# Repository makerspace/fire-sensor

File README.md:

# Fire sensor for Stockholm Makerspace

This ESP32-based sensor monitors the fire-safety system of the [big dust collector](https://wiki.makerspace.se/Sp%C3%A5nsug,_Felder_RL_125) in the [Stockholm Makerspace](https://makerspace.se) Wood Workshop.
If a fire is detected, a POST request is sent to a URL, which will (presumably) then notify people that something bad is happening.

It monitors:

* A temperature sensor.
* A relay for the pressure sensor on the fire-safety system's water tank.
* A distance sensor, used for measuring the amount of dust in the dust bin.
* A relay for the distance sensor.

## Installation

### Pre-requisites

```bash
# Use Linux. It might be compatible with macOS, but likely not.

# Install rust
open https://rustup.rs/

cargo install ldproxy

# Install espup to manage the esp toolchain
cargo install espup --locked

# Install the esp toolchain
espup install

# Install espflash wrapper for cargo
cargo install cargo-espflash

# Clone this repository
git clone https://github.com/makerspace/fire-sensor.git
cd fire-sensor
```

### Flashing the ESP

The ESP supports both flashing via USB, and updates over wifi.

To flash via a connected USB cable, use
```bash
make flash
```

To flash to a powered-on ESP32 module on the same network, use:
```bash
make ota
```

Note: The MAC-address of the ESP32 module is hardcoded in the Makefile.

Note: The ESP32 will connect to the *Stockholm Makerspace Wifi* on startup. You must be on this network to be able to flash it wirelessly.

If the flash failed and the ESP32 cannot start properly, it will automatically revert to the previous firmware.

## Data logging

The ESP32 can connect to an MQTT broker (see config details in `main.rs`) to continuously log all sensor values.
This can also be used to send alerts, or even alerts for if the ESP32 loses power or breaks for some reason.

It will log the following data to the given MQTT topics:

```
sync/devices/{device_id}/status: JSON string, "online" | "offline". Uses MQTT last-will-and-testament to set the status to "offline" if the device goes down.
sync/devices/{device_id}/version: JSON string, "#{git hash} {timestamp}". The git hash of the commit the firmware was last flashed with, and the timestamp of the last build.
sync/dust_collector/{device_id}/temperature: Option<f32>, the temperature in degrees Celcius as given by the attached temperature sensor.
sync/dust_collector/{device_id}/water_pressure: Option<bool>, true when there's positive pressure.
sync/dust_collector/{device_id}/dust_level: Option<u16>, sensor value from the ultrasonic distance sensor.
sync/dust_collector/{device_id}/dust_level_warning_1: Option<bool>, true when the dust level is too high.
sync/dust_collector/{device_id}/dust_level_warning_2: Option<bool>, true when the dust level is very high and the machine will be turned off.
sync/dust_collector/{device_id}/machine_running: Option<bool>, true when the machine is running.
sync/dust_collector/{device_id}/powered_on_too_long: Option<bool>, true when the gates have been opened for too long, and the machine has been turned off automatically.
sync/dust_collector/{device_id}/gates/N/open: Option<bool>, true when the gate is open
```

Where `device_id` is `fire_sensor {MAC ADDRESS OF ESP32}`.

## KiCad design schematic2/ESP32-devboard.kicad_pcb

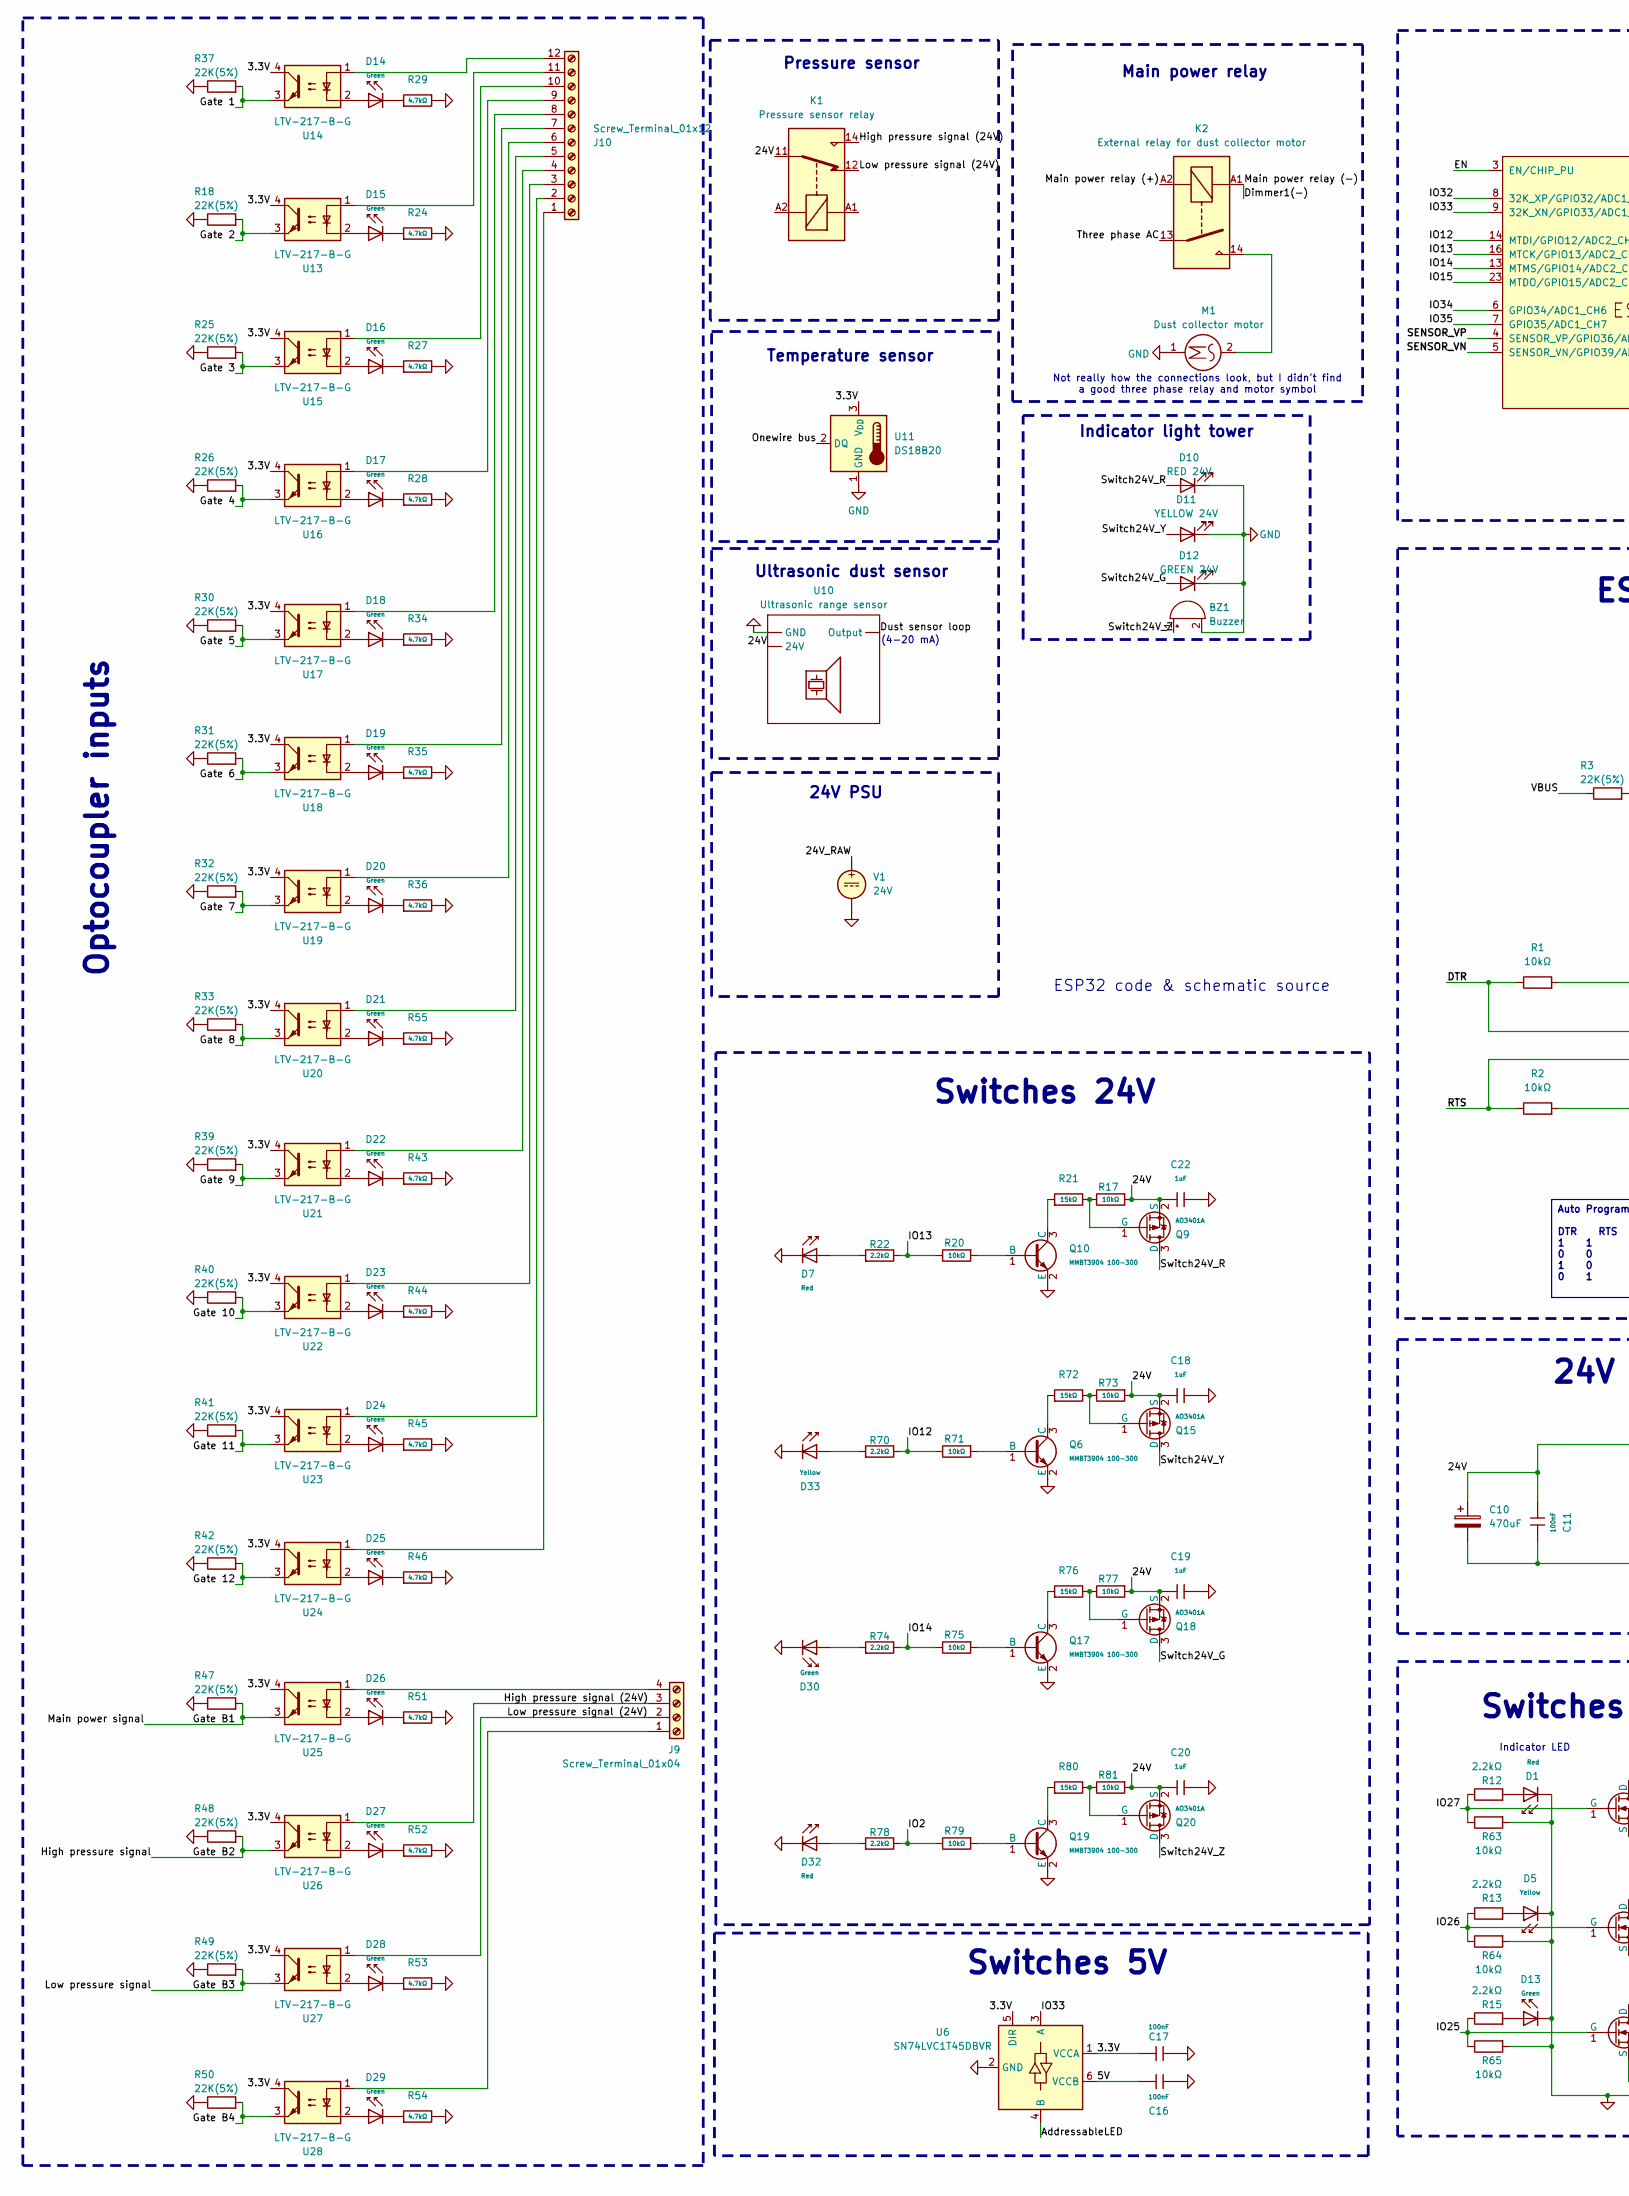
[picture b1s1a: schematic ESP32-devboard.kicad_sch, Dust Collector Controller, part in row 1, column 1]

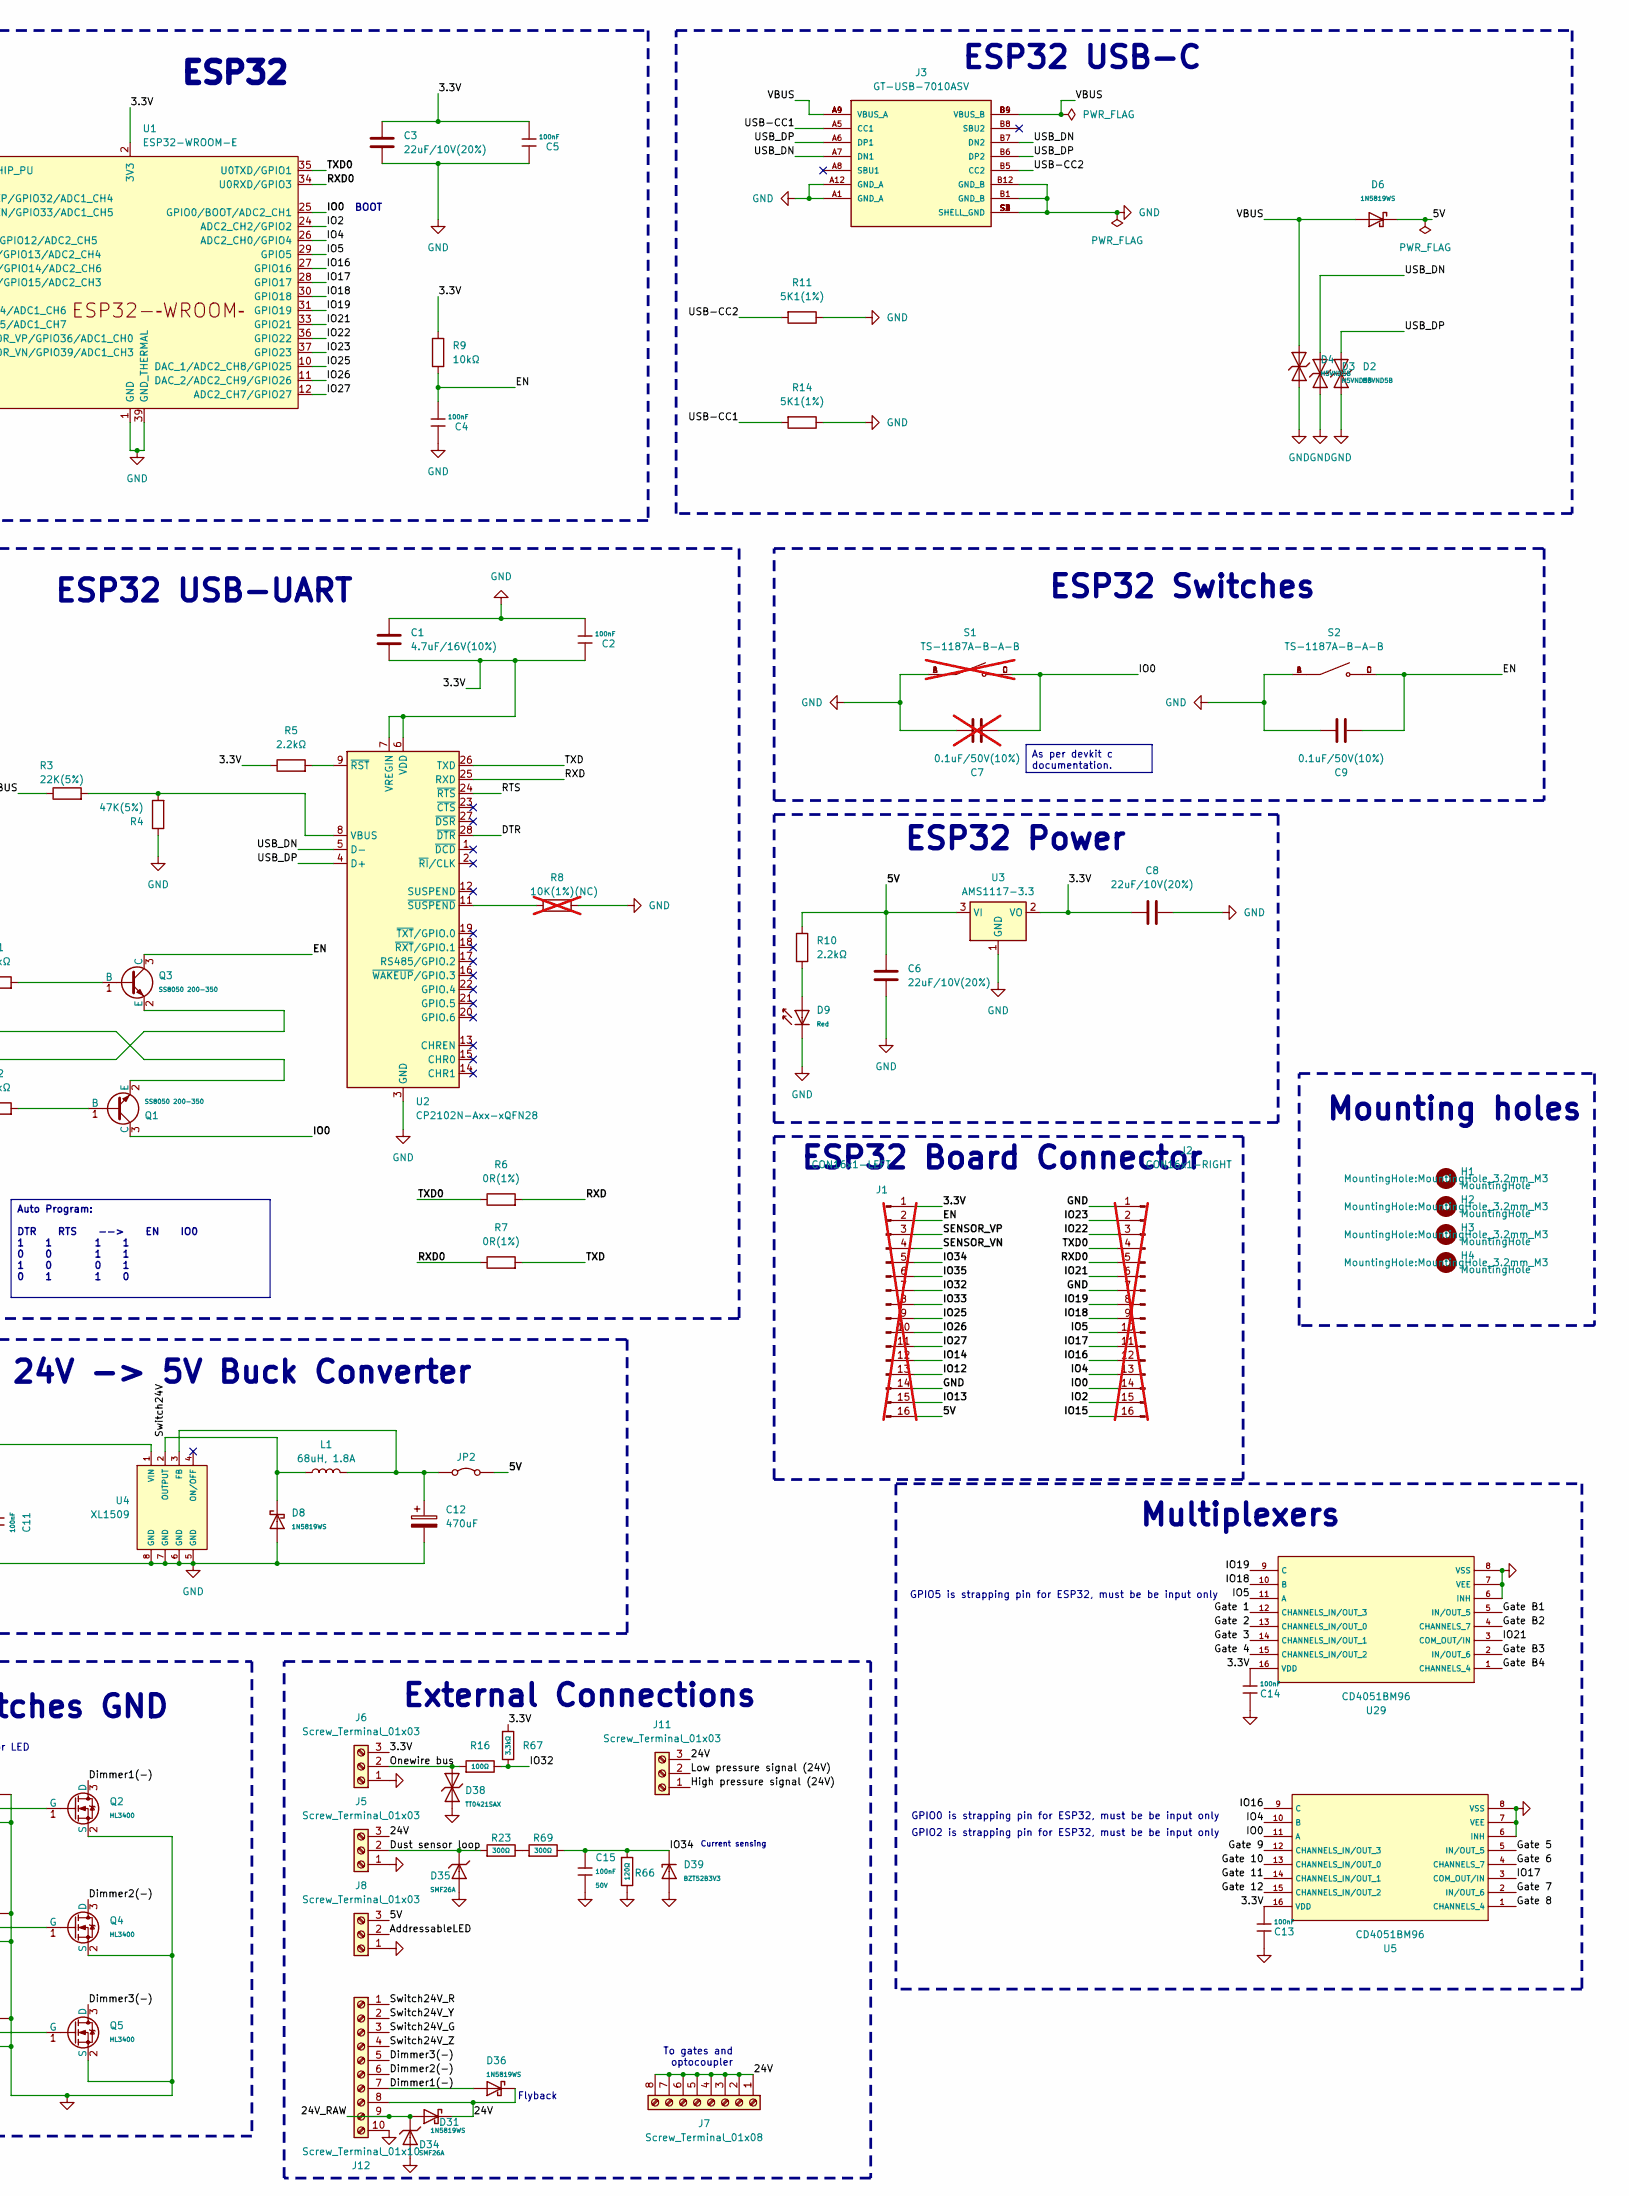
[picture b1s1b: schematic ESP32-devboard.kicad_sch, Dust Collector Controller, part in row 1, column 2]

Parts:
BZ1: Buzzer
C1: 4.7uF/16V(10%); C_0603_1608Metric; LCSC C19666
C2, C4, C5, C11, C13, C14, C15, C16, C17: 100nF; C_0603; Voltage Rated 50V; Tolerance ±10%; Part CC0603KRX7R9BB104; LCSC C14663
C3, C6, C8: 22uF/10V(20%); C_0805_2012Metric; LCSC C45783
C7: 0.1uF/50V(10%); C_0402_1005Metric; LCSC C307331; not fitted
C9: 0.1uF/50V(10%); C_0402_1005Metric; LCSC C307331
C10, C12: 470uF; CP_Radial_D10.0mm_P5.00mm
C18, C19, C20, C22: 1uF; C_0603; Voltage Rated 50V; Tolerance ±10%; Part CL10A105KB8NNNC; LCSC C15849
D1, D7, D9, D32: Red; D_0603; Part KT-0603R; LCSC C2286
D2, D3, D4: H5VND5B; D_SOD-523; Part H5VND5B; LCSC C20615818
D5, D33: Yellow; D_0805; Part KT-0805Y; LCSC C2296
D6, D8, D31, D36: 1N5819WS; D_SOD-323; Forward Voltage (Vf@If) 600mV@1A; Reverse Voltage (Vr) 40V; Part 1N5819WS; LCSC C191023
D10: RED 24V
D11: YELLOW 24V
D12: GREEN 24V
D13, D14, D15, D16, D17, D18, D19, D20, D21, D22, D23, D24, D25, D26, D27, D28, D29, D30: Green; D_0805; Part KT-0805G; LCSC C2297
D34, D35: SMF26A; D_SOD-123FL; Clamping Voltage 42.1V; Voltage - Breakdown 31.9V; Part SMF26A; LCSC C41376090
D38: TT0421SAX; D_DFN0603-2L; Clamping Voltage 4.5V; Voltage Breakdown 9V; Part TT0421SAX; LCSC C5364033
D39: BZT52B3V3; D_SOD-123; Part BZT52B3V3; LCSC C19077392
H1, H2, H3, H4: MountingHole; MountingHole_3.2mm_M3
J1: CON16x1-LEFT; PinSocket_1x16_P2.54mm_Vertical; not fitted
J2: CON16x1-RIGHT; PinSocket_1x16_P2.54mm_Vertical; not fitted
J3: GT-USB-7010ASV; GT-USB-7010; LCSC C2988369
J5, J6, J8, J11: Screw_Terminal_01x03; PinHeader_1x03_P2.54mm_Horizontal
J7: Screw_Terminal_01x08; TerminalBlock_Phoenix_MKDS-1,5-8_1x08_P5.00mm_Horizontal
J9: Screw_Terminal_01x04; TerminalBlock_Phoenix_MKDS-1,5-4_1x04_P5.00mm_Horizontal
J10: Screw_Terminal_01x12; TerminalBlock_Phoenix_MKDS-1,5-12_1x12_P5.00mm_Horizontal
J12: Screw_Terminal_01x10; TerminalBlock_Phoenix_MKDS-1,5-10_1x10_P5.00mm_Horizontal
JP2: Jumper_2_Bridged; PinHeader_1x02_P2.54mm_Vertical
K1: Pressure sensor relay; Relay_SPDT_Fujitsu_FTR-LYCA005x_FormC_Vertical
K2: External relay for dust collector motor; Relay_SPST-NO_Fujitsu_FTR-LYAA005x_FormA_Vertical
L1: 68uH, 1.8A; Inductor C5189964; LCSC C5189964
M1: Dust collector motor
Q1, Q3: SS8050 200-350; Q_SOT-23; Part SS8050(RANGE:200-350); LCSC C2150
Q2, Q4, Q5: HL3400; Q_SOT-23; Part HL3400; LCSC C22469448
Q6, Q10, Q17, Q19: MMBT3904 100-300; Q_SOT-23; Part MMBT3904(RANGE:100-300); LCSC C20526
Q9, Q15, Q18, Q20: AO3401A; Q_SOT-23; Part AO3401A; LCSC C15127
R1, R2, R9, R63, R64, R65: 10kΩ; R_0603; LCSC C25804
R3, R18, R25, R26, R30, R31, R32, R33, R37, R39, R40, R41, R42, R47, R48, R49, R50: 22K(5%); R_0603; LCSC C31850
R4: 47K(5%); R_0603; LCSC C25819
R5, R10, R12, R13, R15: 2.2kΩ; R_0603; LCSC C4190
R6, R7: 0R(1%); C_0402_1005Metric; LCSC C17168
R8: 10K(1%)(NC); C_0603_1608Metric; LCSC C25804; not fitted
R11, R14: 5K1(1%); R_0402_1005Metric; LCSC C25905
R16: 100Ω; R_0402; Overload Voltage (Max) 50V; Tolerance ±1%; Part 0402WGF1000TCE; LCSC C25076
R17, R20, R71, R73, R75, R77, R79, R81: 10kΩ; R_0603; Overload Voltage (Max) 75V; Tolerance ±1%; Part 0603WAF1002T5E; LCSC C25804
R21, R72, R76, R80: 15kΩ; R_0603; Overload Voltage (Max) 75V; Tolerance ±1%; Part 0603WAF1502T5E; LCSC C22809
R22, R70, R74, R78: 2.2kΩ; R_0603; Overload Voltage (Max) 75V; Tolerance ±1%; Part 0603WAF2201T5E; LCSC C4190
R23, R69: 300Ω; R_1206; Overload Voltage (Max) 200V; Tolerance ±1%; Part 1206W4F3000T5E; LCSC C17887
R24, R27, R28, R29, R34, R35, R36, R43, R44, R45, R46, R51, R52, R53, R54, R55: 4.7kΩ; R_0603; Overload Voltage (Max) 75V; Tolerance ±1%; Part 0603WAF4701T5E; LCSC C23162
R66: 120Ω; R_0603; Overload Voltage (Max) 75V; Tolerance ±1%; Part 0603WAF1200T5E; LCSC C22787
R67: 3.3kΩ; R_0402; Overload Voltage (Max) 50V; Tolerance ±1%; Part 0402WGF3301TCE; LCSC C25890
S1: TS-1187A-B-A-B; SW_TS-1187A-B-A-B; PARTREV A0; LCSC C318884; not fitted
S2: TS-1187A-B-A-B; SW_TS-1187A-B-A-B; PARTREV A0; LCSC C318884
U1: ESP32-WROOM-E; ESP32-WROOM-32E; LCSC C701342
U2: CP2102N-Axx-xQFN28; QFN-28-1EP_5x5mm_P0.5mm_EP3.35x3.35mm; LCSC C964632
U3: AMS1117-3.3; SOT-223-3_TabPin2; LCSC C6186
U4: XL1509; SOIC-8_L5.0-W4.0-P1.27-LS6.0-BL; Output Voltage 5V; Input Voltage 4.5V~40V; Part XL1509-5.0E1; LCSC C61063
U5, U29: CD4051BM96; SOIC-16_L9.9-W3.9-P1.27-LS6.0-BL; Supply Voltage 3V~20V; Part CD4051BM96; LCSC C21379
U6: SN74LVC1T45DBVR; SOT-23-6; LCSC C7843
U10: Ultrasonic range sensor
U11: DS18B20; TO-92_Inline
U13, U14, U15, U16, U17, U18, U19, U20, U21, U22, U23, U24, U25, U26, U27, U28: LTV-217-B-G; SOP-4_4.4x2.6mm_P1.27mm; Part LTV-217-B-G; LCSC C115450
V1: 24V

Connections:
/3.3V: C1.2, C2.2, C3.1, C5.1, C8.1, C13.1, C14.1, C17.1, J1.1, J6.3, R5.1, R9.1, R67.1, U1.2 (3V3), U2.6 (VDD), U2.7 (VREGIN), U3.2 (VO), U5.16 (VDD), U6.1 (VCCA), U6.5 (DIR), U11.3 (V_{DD}), U13.4, U14.4, U15.4, U16.4, U17.4, U18.4, U19.4, U20.4, U21.4, U22.4, U23.4, U24.4, U25.4, U26.4, U27.4, U28.4, U29.16 (VDD)
/5V: C6.1, C16.1, D6.1, J1.16, J8.3, JP2.2 (B), R10.1, U3.3 (VI), U6.6 (VCCB)
/24V: C10.1, C11.2, C18.1, C19.1, C20.1, C22.1, D31.1, D36.1, J5.3, J7.1, J7.2, J7.3, J7.4, J7.5, J7.6, J7.7, J7.8, J11.3, J12.8, K1.11, Q9.2 (S), Q15.2 (S), Q18.2 (S), Q20.2 (S), R17.1, R73.1, R77.1, R81.1, U4.1 (VIN), U10.
/24V_RAW: D31.2, D34.1, J12.9, V1.1
/AddressableLED: J8.2, U6.4 (B)
/DTR: Q1.2 (E), R1.1, U2.28 (~DTR)
/Dimmer1(-): D36.2, J12.7, K2.A1, Q2.3 (D)
/Dimmer2(-): J12.6, Q4.3 (D)
/Dimmer3(-): J12.5, Q5.3 (D)
/Dust sensor loop: D35.1, J5.2, R23.1, U10.
/EN: C4.1, C9.1, J1.2, Q3.3 (C), R9.2, S2.C, S2.D, U1.3 (EN/CHIP_PU)
/Gate 1: R37.2, U14.3, U29.12 (CHANNELS_IN/OUT_3)
/Gate 2: R18.2, U13.3, U29.13 (CHANNELS_IN/OUT_0)
/Gate 3: R25.2, U15.3, U29.14 (CHANNELS_IN/OUT_1)
/Gate 4: R26.2, U16.3, U29.15 (CHANNELS_IN/OUT_2)
/Gate 5: R30.2, U5.5 (IN/OUT_5), U17.3
/Gate 6: R31.2, U5.4 (CHANNELS_7), U18.3
/Gate 7: R32.2, U5.2 (IN/OUT_6), U19.3
/Gate 8: R33.2, U5.1 (CHANNELS_4), U20.3
/Gate 9: R39.2, U5.12 (CHANNELS_IN/OUT_3), U21.3
/Gate 10: R40.2, U5.13 (CHANNELS_IN/OUT_0), U22.3
/Gate 11: R41.2, U5.14 (CHANNELS_IN/OUT_1), U23.3
/Gate 12: R42.2, U5.15 (CHANNELS_IN/OUT_2), U24.3
/Gate B1: R47.2, U25.3, U29.5 (IN/OUT_5)
/Gate B2: R48.2, U26.3, U29.4 (CHANNELS_7)
/Gate B3: R49.2, U27.3, U29.2 (IN/OUT_6)
/Gate B4: R50.2, U28.3, U29.1 (CHANNELS_4)
/High pressure signal (24V): J9.3, J11.1, K1.14, U26.1
/IO0: C7.1, J2.14, Q1.3 (C), S1.C, S1.D, U1.25 (GPIO0/BOOT/ADC2_CH1), U5.11 (A)
/IO2: J2.15, R78.2, R79.2, U1.24 (ADC2_CH2/GPIO2)
/IO4: J2.13, U1.26 (ADC2_CH0/GPIO4), U5.10 (B)
/IO5: J2.10, U1.29 (GPIO5), U29.11 (A)
/IO12: J1.13, R70.2, R71.2, U1.14 (MTDI/GPIO12/ADC2_CH5)
/IO13: J1.15, R20.2, R22.2, U1.16 (MTCK/GPIO13/ADC2_CH4)
/IO14: J1.12, R74.2, R75.2, U1.13 (MTMS/GPIO14/ADC2_CH6)
/IO15: J2.16, U1.23 (MTDO/GPIO15/ADC2_CH3)
/IO16: J2.12, U1.27 (GPIO16), U5.9 (C)
/IO17: J2.11, U1.28 (GPIO17), U5.3 (COM_OUT/IN)
/IO18: J2.9, U1.30 (GPIO18), U29.10 (B)
/IO19: J2.8, U1.31 (GPIO19), U29.9 (C)
/IO21: J2.6, U1.33 (GPIO21), U29.3 (COM_OUT/IN)
/IO22: J2.3, U1.36 (GPIO22)
/IO23: J2.2, U1.37 (GPIO23)
/IO25: J1.9, Q5.1 (G), R15.1, R65.1, U1.10 (DAC_1/ADC2_CH8/GPIO25)
/IO26: J1.10, Q4.1 (G), R13.1, R64.1, U1.11 (DAC_2/ADC2_CH9/GPIO26)
/IO27: J1.11, Q2.1 (G), R12.1, R63.1, U1.12 (ADC2_CH7/GPIO27)
/IO32: J1.7, R16.2, R67.2, U1.8 (32K_XP/GPIO32/ADC1_CH4)
/IO33: J1.8, U1.9 (32K_XN/GPIO33/ADC1_CH5), U6.3 (A)
/IO34: C15.1, D39.1, J1.5, R66.1, R69.2, U1.6 (GPIO34/ADC1_CH6)
/IO35: J1.6, U1.7 (GPIO35/ADC1_CH7)
/Low pressure signal (24V): J9.2, J11.2, K1.12, U27.1
/Onewire bus: D38.2, J6.2, R16.1, U11.2 (DQ)
/RTS: Q3.2 (E), R2.1, U2.24 (~RTS)
/RXD: R6.2, U2.25 (RXD)
/RXD0: J2.5, R7.1, U1.34 (U0RXD/GPIO3)
/SENSOR_VN: J1.4, U1.5 (SENSOR_VN/GPIO39/ADC1_CH3)
/SENSOR_VP: J1.3, U1.4 (SENSOR_VP/GPIO36/ADC1_CH0)
/Switch24V: D8.1, L1.1, U4.2 (OUTPUT)
/Switch24V_G: D12.2 (A), J12.3, Q18.3 (D)
/Switch24V_R: D10.2 (A), J12.1, Q9.3 (D)
/Switch24V_Y: D11.2 (A), J12.2, Q15.3 (D)
/Switch24V_Z: BZ1.1 (+), J12.4, Q20.3 (D)
/TXD: R7.2, U2.26 (TXD)
/TXD0: J2.4, R6.1, U1.35 (U0TXD/GPIO1)
/USB-CC1: J3.A5 (CC1), R14.2
/USB-CC2: J3.B5 (CC2), R11.2
/USB_DN: D3.2, J3.A7 (DN1), J3.B7 (DN2), U2.5 (D-)
/USB_DP: D2.2, J3.A6 (DP1), J3.B6 (DP2), U2.4 (D+)
/VBUS: D4.2, D6.2, J3.A4 (VBUS_A), J3.A9 (VBUS_A), J3.B4 (VBUS_B), J3.B9 (VBUS_B), R3.1
GND: BZ1.2 (-), C1.1, C2.1, C3.2, C4.2, C5.2, C6.2, C7.2, C8.2, C9.2, C10.2, C11.1, C12.2, C13.2, C14.2, C15.2, C16.2, C17.2, C18.2, C19.2, C20.2, C22.2, D1.1, D2.1, D3.1, D4.1, D5.1, D7.1, D8.2, D9.1, D10.1 (K), D11.1 (K), D12.1 (K), D13.1, D30.1, D32.1, D33.1, D34.2, D35.2, D38.1, D39.2, J1.14, J2.1, J2.7, J3.A1 (GND_A), J3.A12 (GND_A), J3.B1 (GND_B), J3.B12 (GND_B), J3.S1 (SHELL_GND), J3.S2 (SHELL_GND), J3.S3 (SHELL_GND), J3.S4 (SHELL_GND), J5.1, J6.1, J8.1, J12.10, M1.1, Q2.2 (S), Q4.2 (S), Q5.2 (S), Q6.2 (E), Q10.2 (E), Q17.2 (E), Q19.2 (E), R4.1, R8.2, R11.1, R14.1, R18.1, R24.2, R25.1, R26.1, R27.2, R28.2, R29.2, R30.1, R31.1, R32.1, R33.1, R34.2, R35.2, R36.2, R37.1, R39.1, R40.1, R41.1, R42.1, R43.2, R44.2, R45.2, R46.2, R47.1, R48.1, R49.1, R50.1, R51.2, R52.2, R53.2, R54.2, R55.2, R63.2, R64.2, R65.2, R66.2, S1.A, S1.B, S2.A, S2.B, U1.1 (GND), U1.15 (GND), U1.38 (GND), U1.39 (GND_THERMAL), U2.3 (GND), U2.29 (GND), U3.1 (GND), U4.5 (GND), U4.6 (GND), U4.7 (GND), U4.8 (GND), U5.6 (INH), U5.7 (VEE), U5.8 (VSS), U6.2 (GND), U10., U11.1 (GND), U29.6 (INH), U29.7 (VEE), U29.8 (VSS), V1.2
unnamed: D1.2, R12.2
unnamed: D5.2, R13.2
unnamed: D7.2, R22.1
unnamed: D9.2, R10.2
unnamed: D13.2, R15.2
unnamed: D14.1, R29.1
unnamed: D14.2, U14.2
unnamed: D15.1, R24.1
unnamed: D15.2, U13.2
unnamed: D16.1, R27.1
unnamed: D16.2, U15.2
unnamed: D17.1, R28.1
unnamed: D17.2, U16.2
unnamed: D18.1, R34.1
unnamed: D18.2, U17.2
unnamed: D19.1, R35.1
unnamed: D19.2, U18.2
unnamed: D20.1, R36.1
unnamed: D20.2, U19.2
unnamed: D21.1, R55.1
unnamed: D21.2, U20.2
unnamed: D22.1, R43.1
unnamed: D22.2, U21.2
unnamed: D23.1, R44.1
unnamed: D23.2, U22.2
unnamed: D24.1, R45.1
unnamed: D24.2, U23.2
unnamed: D25.1, R46.1
unnamed: D25.2, U24.2
unnamed: D26.1, R51.1
unnamed: D26.2, U25.2
unnamed: D27.1, R52.1
unnamed: D27.2, U26.2
unnamed: D28.1, R53.1
unnamed: D28.2, U27.2
unnamed: D29.1, R54.1
unnamed: D29.2, U28.2
unnamed: D30.2, R74.1
unnamed: D32.2, R78.1
unnamed: D33.2, R70.1
unnamed: J9.1, U28.1
unnamed: J9.4, U25.1
unnamed: J10.1, U24.1
unnamed: J10.2, U23.1
unnamed: J10.3, U22.1
unnamed: J10.4, U21.1
unnamed: J10.5, U20.1
unnamed: J10.6, U19.1
unnamed: J10.7, U18.1
unnamed: J10.8, U17.1
unnamed: J10.9, U16.1
unnamed: J10.10, U15.1
unnamed: J10.11, U13.1
unnamed: J10.12, U14.1
unnamed: C12.1, JP2.1 (A), L1.2, U4.3 (FB)
unnamed: K2.14, M1.2
unnamed: Q1.1 (B), R2.2
unnamed: Q3.1 (B), R1.2
unnamed: Q6.1 (B), R71.1
unnamed: Q6.3 (C), R72.1
unnamed: Q9.1 (G), R17.2, R21.2
unnamed: Q10.1 (B), R20.1
unnamed: Q10.3 (C), R21.1
unnamed: Q15.1 (G), R72.2, R73.2
unnamed: Q17.1 (B), R75.1
unnamed: Q17.3 (C), R76.1
unnamed: Q18.1 (G), R76.2, R77.2
unnamed: Q19.1 (B), R79.1
unnamed: Q19.3 (C), R80.1
unnamed: Q20.1 (G), R80.2, R81.2
unnamed: R23.2, R69.1
unnamed: R3.2, R4.2, U2.8 (VBUS)
unnamed: R5.2, U2.9 (~RST)
unnamed: R8.1, U2.11 (~SUSPEND)

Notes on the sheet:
Switches 24V
Indicator LED
ESP32 Power
ESP32 Board Connector
ESP32 Switches
24V PSU
GPIO0 is strapping pin for ESP32, must be be input only
Flyback
24V -> 5V Buck Converter
Temperature sensor
(4-20 mA)
To gates and optocoupler
ESP32 code & schematic source
Multiplexers
Current sensing
GPIO5 is strapping pin for ESP32, must be be input only
Mounting holes
Ultrasonic dust sensor
ESP32 USB-C
GPIO2 is strapping pin for ESP32, must be be input only
Not really how the connections look, but I didn't find a good three phase relay and motor symbol
ESP32
Main power relay
External Connections
Indicator light tower
BOOT
Optocoupler inputs
ESP32 USB-UART
Pressure sensor
Switches 5V
Switches GND
Auto Program: DTR RTS --> EN IO0 1 1 1 1 0 0 1 1 1 0 0 1 0 1 1 0
As per devkit c documentation.

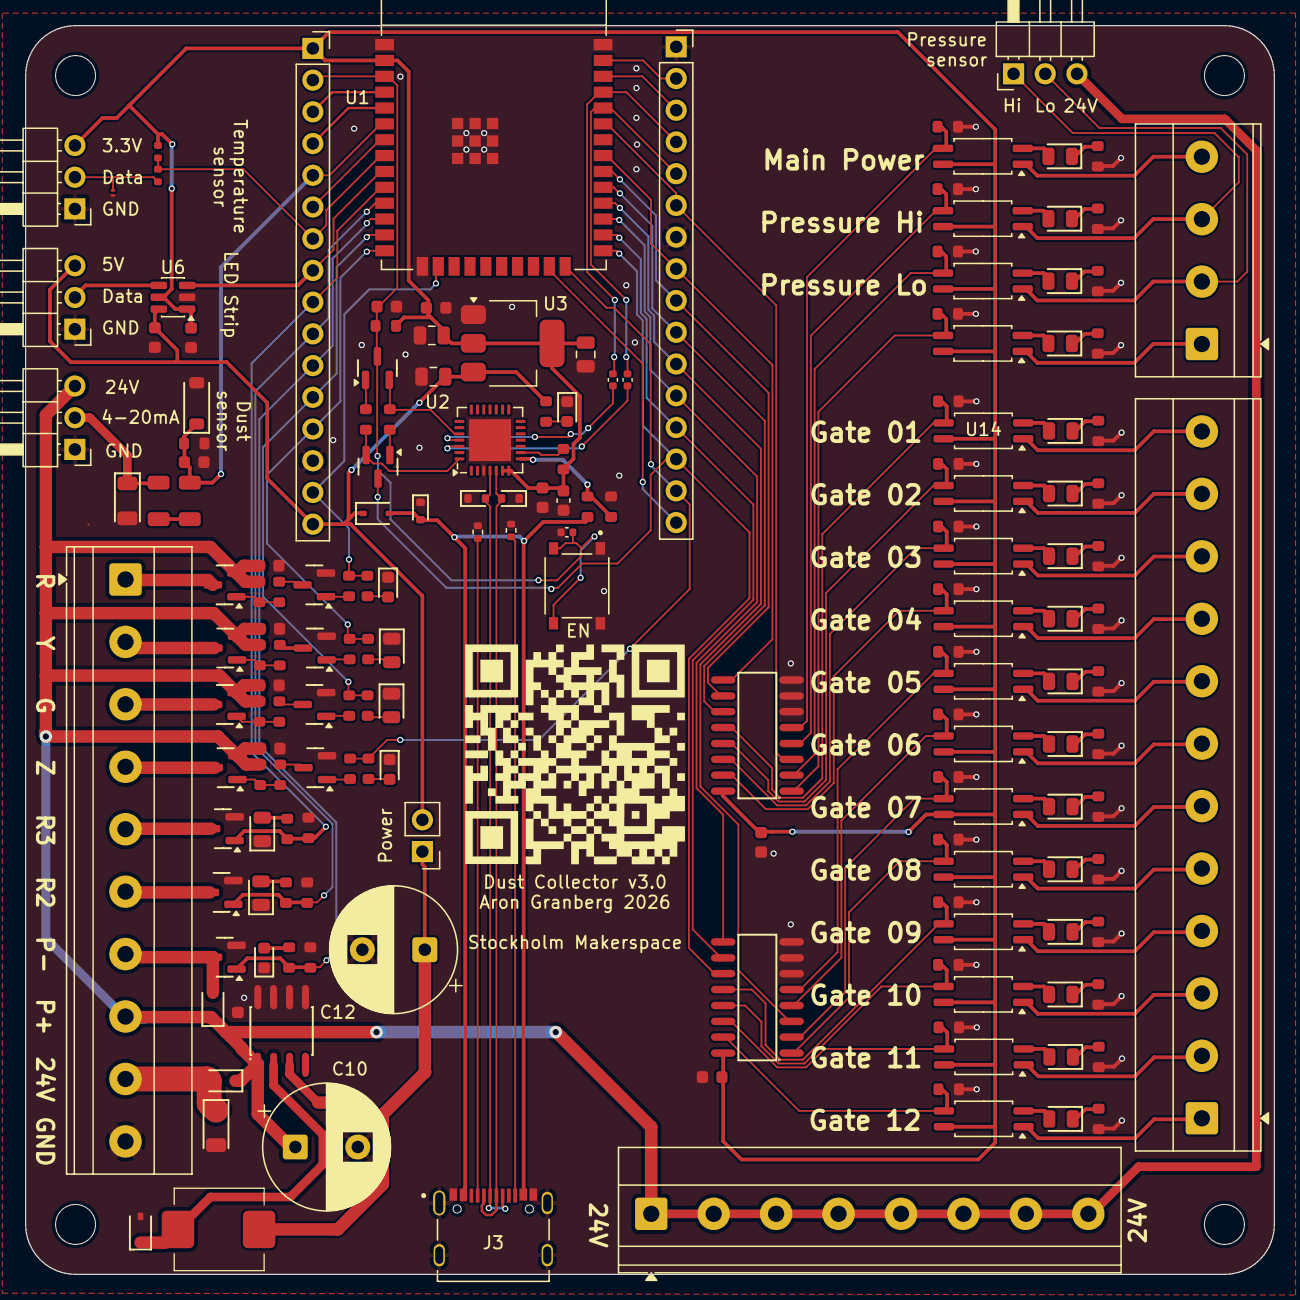
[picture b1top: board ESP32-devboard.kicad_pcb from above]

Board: 2 copper layers, 100.0 x 100.0 mm, 179 parts (0 on the bottom side), 142 nets.

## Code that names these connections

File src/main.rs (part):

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    let is_wokwi_simulator = check_is_wokwi()?;

    // Pin assignments
    let temperature_sensor_pin = peripherals.pins.gpio32;
    let dust_sensor_analog_pin = peripherals.pins.gpio34;
    let power_controller_pin = peripherals.pins.gpio27;
    let dimmer2_pin = peripherals.pins.gpio26;
    let debug_led_pin = peripherals.pins.gpio25;

    let indicator_red_pin = peripherals.pins.gpio13;
    let indicator_yellow_pin = peripherals.pins.gpio12;
    let indicator_green_pin = peripherals.pins.gpio14;
    let indicator_sound_pin = peripherals.pins.gpio2;

    let multiplexer1_data_pin = peripherals.pins.gpio21;
    let multiplexer1_selector_pin_0 = peripherals.pins.gpio5;
    let multiplexer1_selector_pin_1 = peripherals.pins.gpio18;
    let multiplexer1_selector_pin_2 = peripherals.pins.gpio19;

    let multiplexer2_data_pin = peripherals.pins.gpio17;
    let led_strip_mosi_pin = peripherals.pins.gpio33;
    let led_strip_sclk_pin = peripherals.pins.gpio22;
    let led_strip_spi = peripherals.spi2;

    let multiplexer2_selector_pin_0 = peripherals.pins.gpio0;
    let multiplexer2_selector_pin_1 = peripherals.pins.gpio4;
    let multiplexer2_selector_pin_2 = peripherals.pins.gpio16;

    // Multiplexer channel assignments
    let main_power_relay_channel = 5;
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
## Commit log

2025-11-09 Initial commit.
2025-11-13 Improve code with new pins and various improvements.
2025-11-13 Update README.
2025-11-13 Update schematic.
2025-11-18 Make more resilient against missing sensors.
2025-11-19 Clean up code a bit, and change pins around to match the schematic.
2025-11-26 Various improvements.
2025-11-26 Clean up dependencies.
2025-11-26 When machine turns off due to safety relays, ignore open gates individually instead of having to close all gates to get it working again.
2026-02-19 WIP on new schematic
2026-02-21 Schematic updates
2026-02-24 Schematic updates - Ordered from JLCPCB
2026-03-07 Organize schematic
2026-03-07 Update code to fit new pcb
2026-03-15 Add ESD protection and other safety improvements
2026-03-21 Final tweaks. Ordered from JLCPCB
2026-04-03 Improvements
2026-04-03 WIP on leds
2026-04-03 Improve led strip
2026-04-03 Tweak led animation
2026-04-04 Minor tweaks
